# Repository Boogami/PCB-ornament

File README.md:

# Christmas PCB ornament 🎄🎁🎅🏻

This project features a unique Christmas-themed printed circuit board (PCB) ornament. The ornament is composed of two distinct parts: a red colored PCB and a laser-cut wooden overlay. The PCB, serves as the background and is embellished with festive graphics, including bells and a prominent snowflake design. The wooden overlay, precisely laser-cut, frames the PCB and includes decorative elements such as mistletoe leaves and berries, adding a touch of traditional holiday charm. This innovative blend of technology and traditional holiday motifs makes for a distinctive and eye-catching Christmas ornament.

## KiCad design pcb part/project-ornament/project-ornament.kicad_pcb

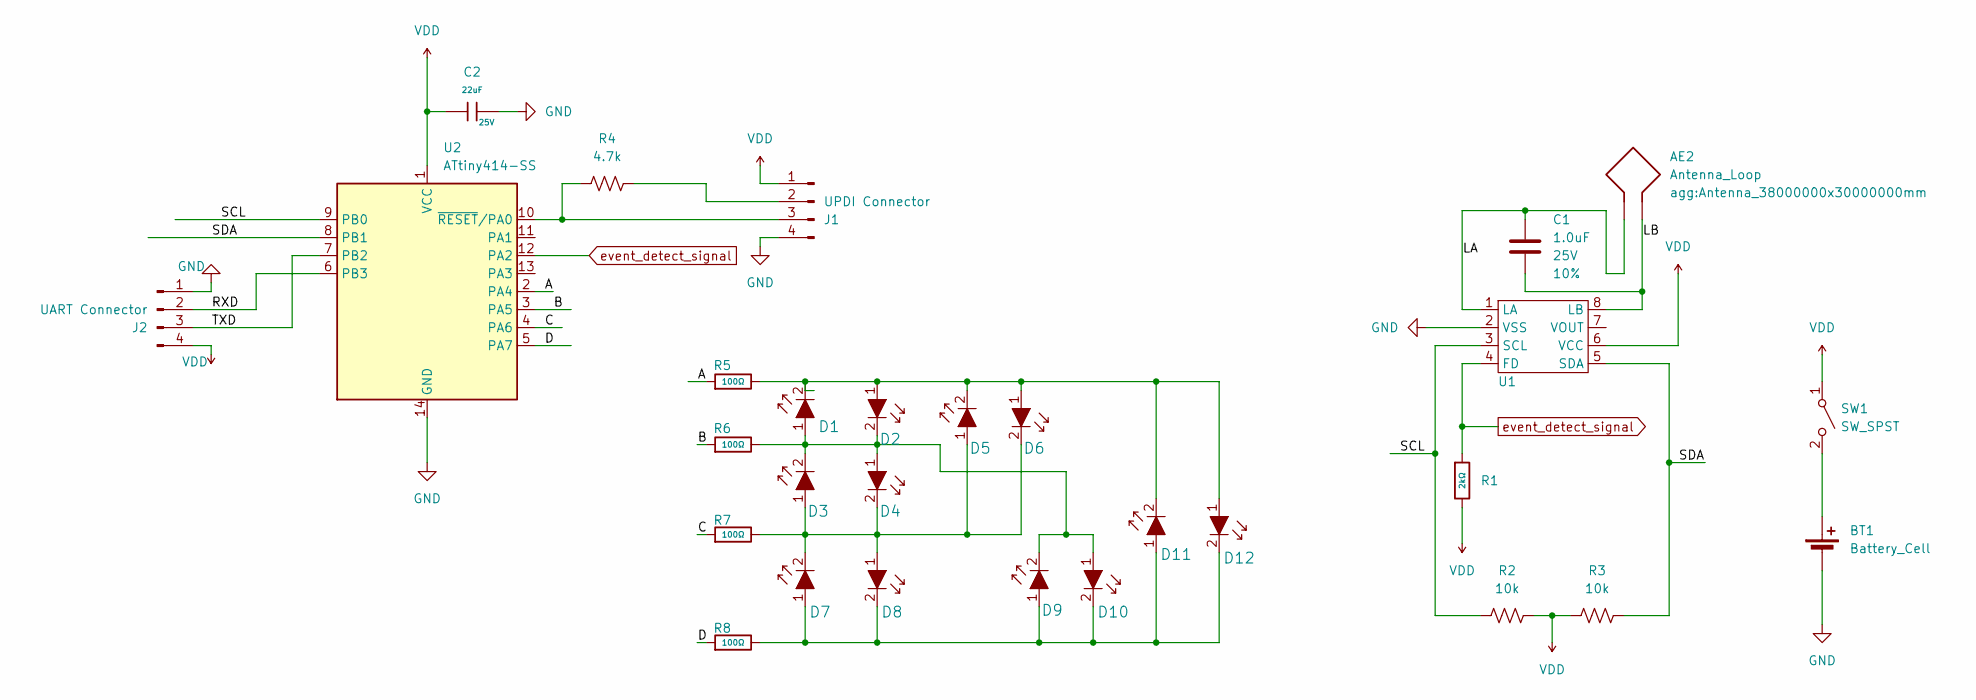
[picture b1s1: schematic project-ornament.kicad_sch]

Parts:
AE2: Antenna_Loop; Antenna_38000000x30000000mm
BT1: Battery_Cell; BatteryHolder_Multicomp_BC-2001_1x2032
C1: 1.0uF; C_0805_2012Metric; Voltage 25V; Tolerance 10%
C2: 22uF; C_0805; Voltage Rated 25V; Tolerance ±20%; Part CL21A226MAQNNNE; LCSC C45783
D1, D2, D3, D4, D5, D6, D7, D8, D9, D10, D11, D12: LTST-C171KGKT; 0805; MPN LTST-C171KGKT; Digi-Key_PN 160-1426-1-ND
J1: UPDI Connector; Harwin_M20-89004xx_1x04_P2.54mm_Horizontal
J2: UART Connector; Harwin_M20-89004xx_1x04_P2.54mm_Horizontal
R1: 2kΩ; R_0603; Overload Voltage (Max) 75V; Tolerance ±1%; Part 0603WAF2001T5E; LCSC C22975
R2, R3: 10k; R_0603_1608Metric
R4: 4.7k; R_0603_1608Metric
R5, R6, R7, R8: 100Ω; R_0805; Overload Voltage (Max) 150V; Tolerance ±1%; Part 0805W8F1000T5E; LCSC C17408
SW1: SW_SPST; SW_SPDT_PCM12
U1: TSSOP-8_3x3mm_P0.65mm
U2: ATtiny414-SS; SOIC-14_3.9x8.7mm_P1.27mm

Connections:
/A: R5.1, U2.2 (PA4)
/B: R6.1, U2.3 (PA5)
/C: R7.1, U2.4 (PA6)
/D: R8.1, U2.5 (PA7)
/LA: AE2.1, C1.1, U1.1 (LA)
/LB: AE2.2, C1.2, U1.8 (LB)
/RXD: J2.2, U2.6 (PB3)
/SCL: R2.2, U1.3 (SCL), U2.9 (PB0)
/SDA: R3.1, U1.5 (SDA), U2.8 (PB1)
/TXD: J2.3, U2.7 (PB2)
GND: BT1.2 (-), C2.2, J1.4, J2.1, U1.2 (VSS), U2.14 (GND)
unnamed: BT1.1 (+), SW1.2 (B)
unnamed: D1.1, D2.2, D3.2, D4.1, D9.2, D10.1, R6.2
unnamed: D1.2, D2.1, D5.2, D6.1, D11.2, D12.1, R5.2
unnamed: D3.1, D4.2, D5.1, D6.2, D7.2, D8.1, R7.2
unnamed: D7.1, D8.2, D9.1, D10.2, D11.1, D12.2, R8.2
unnamed: J1.2, R4.2
unnamed: J1.3, R4.1, U2.10 (~RESET/PA0)
VDD: C2.1, J1.1, J2.4, R1.2, R2.1, R3.2, SW1.1 (A), U1.6 (VCC), U2.1 (VCC)
event_detect_signal: R1.1, U1.4 (FD), U2.12 (PA2)

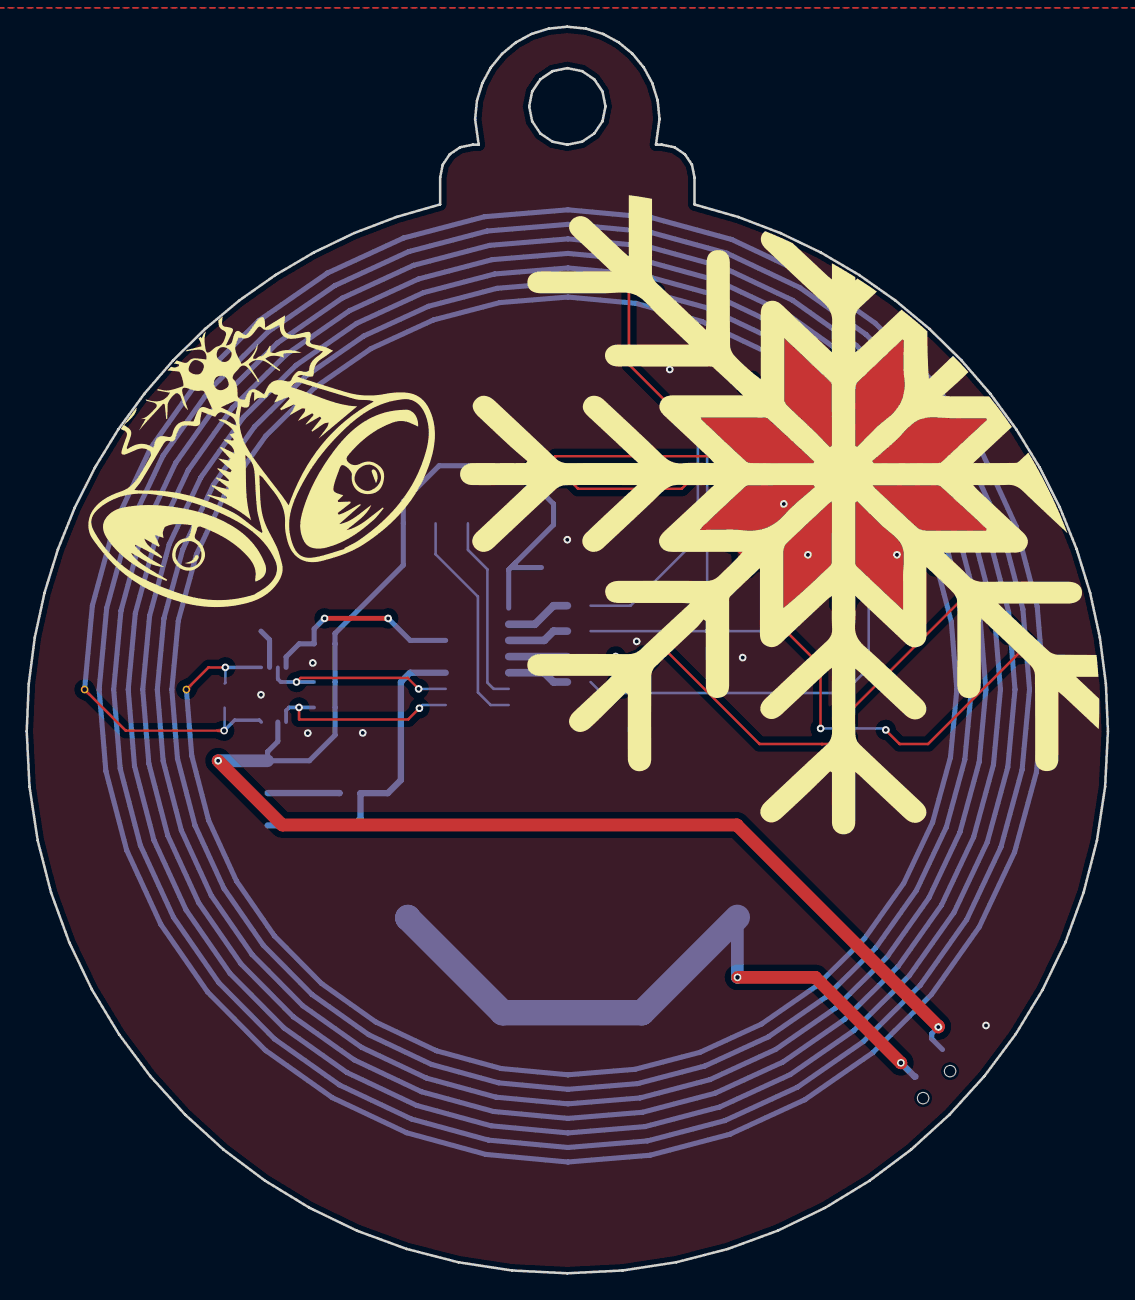
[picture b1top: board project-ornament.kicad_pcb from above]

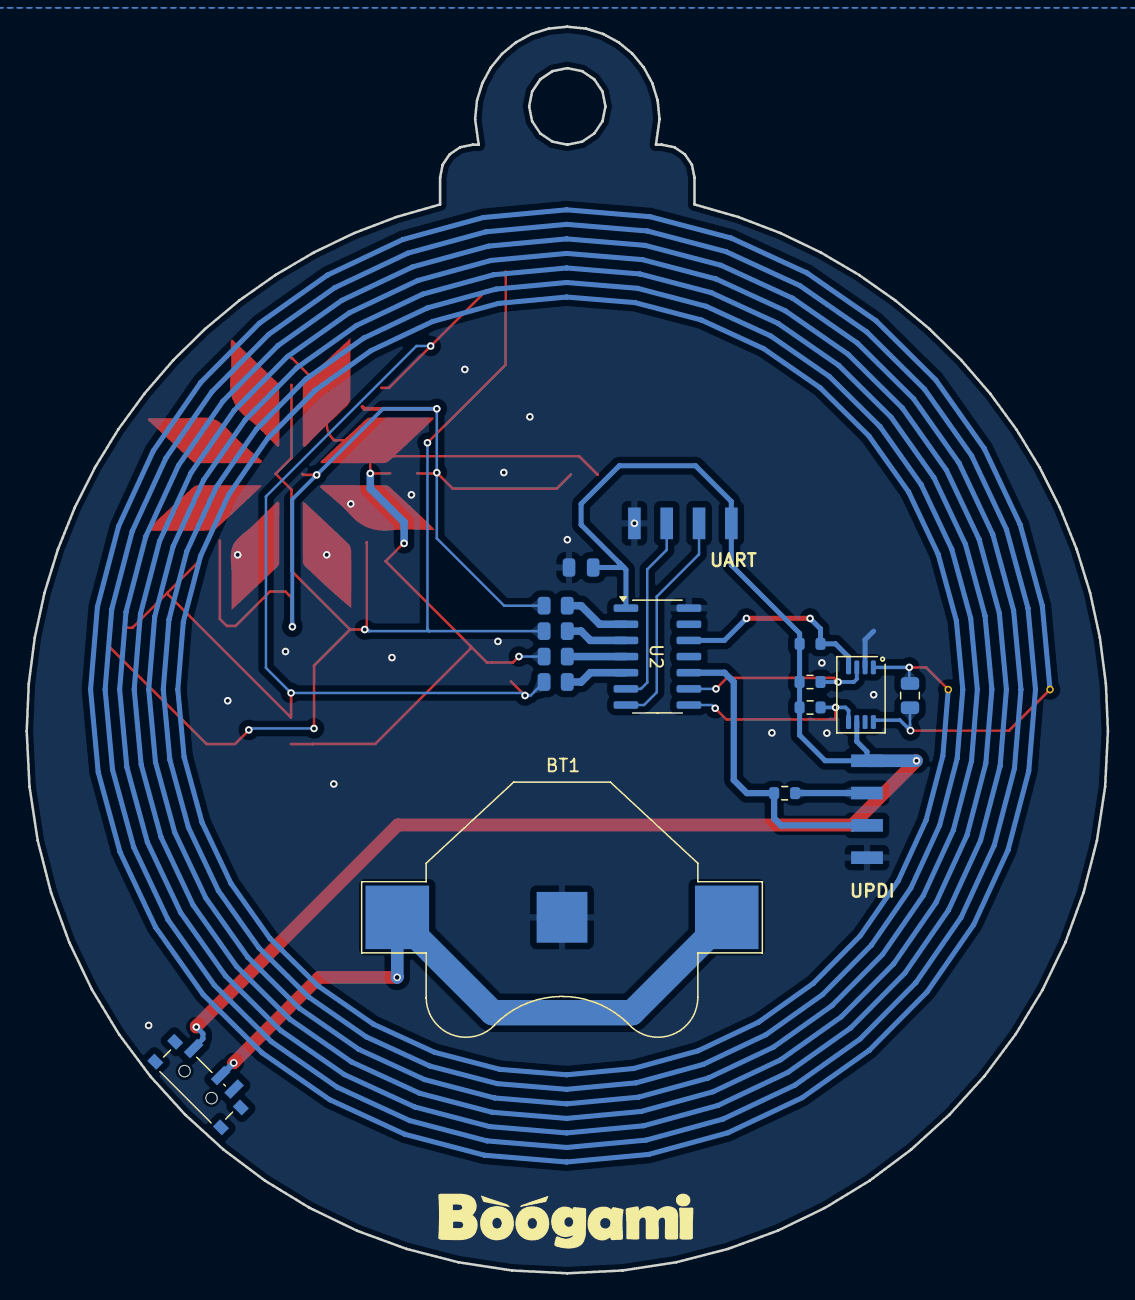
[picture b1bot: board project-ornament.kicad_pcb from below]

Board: 2 copper layers, 85.0 x 98.0 mm, 29 parts (16 on the bottom side), 20 nets.

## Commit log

2024-12-24 Added images
